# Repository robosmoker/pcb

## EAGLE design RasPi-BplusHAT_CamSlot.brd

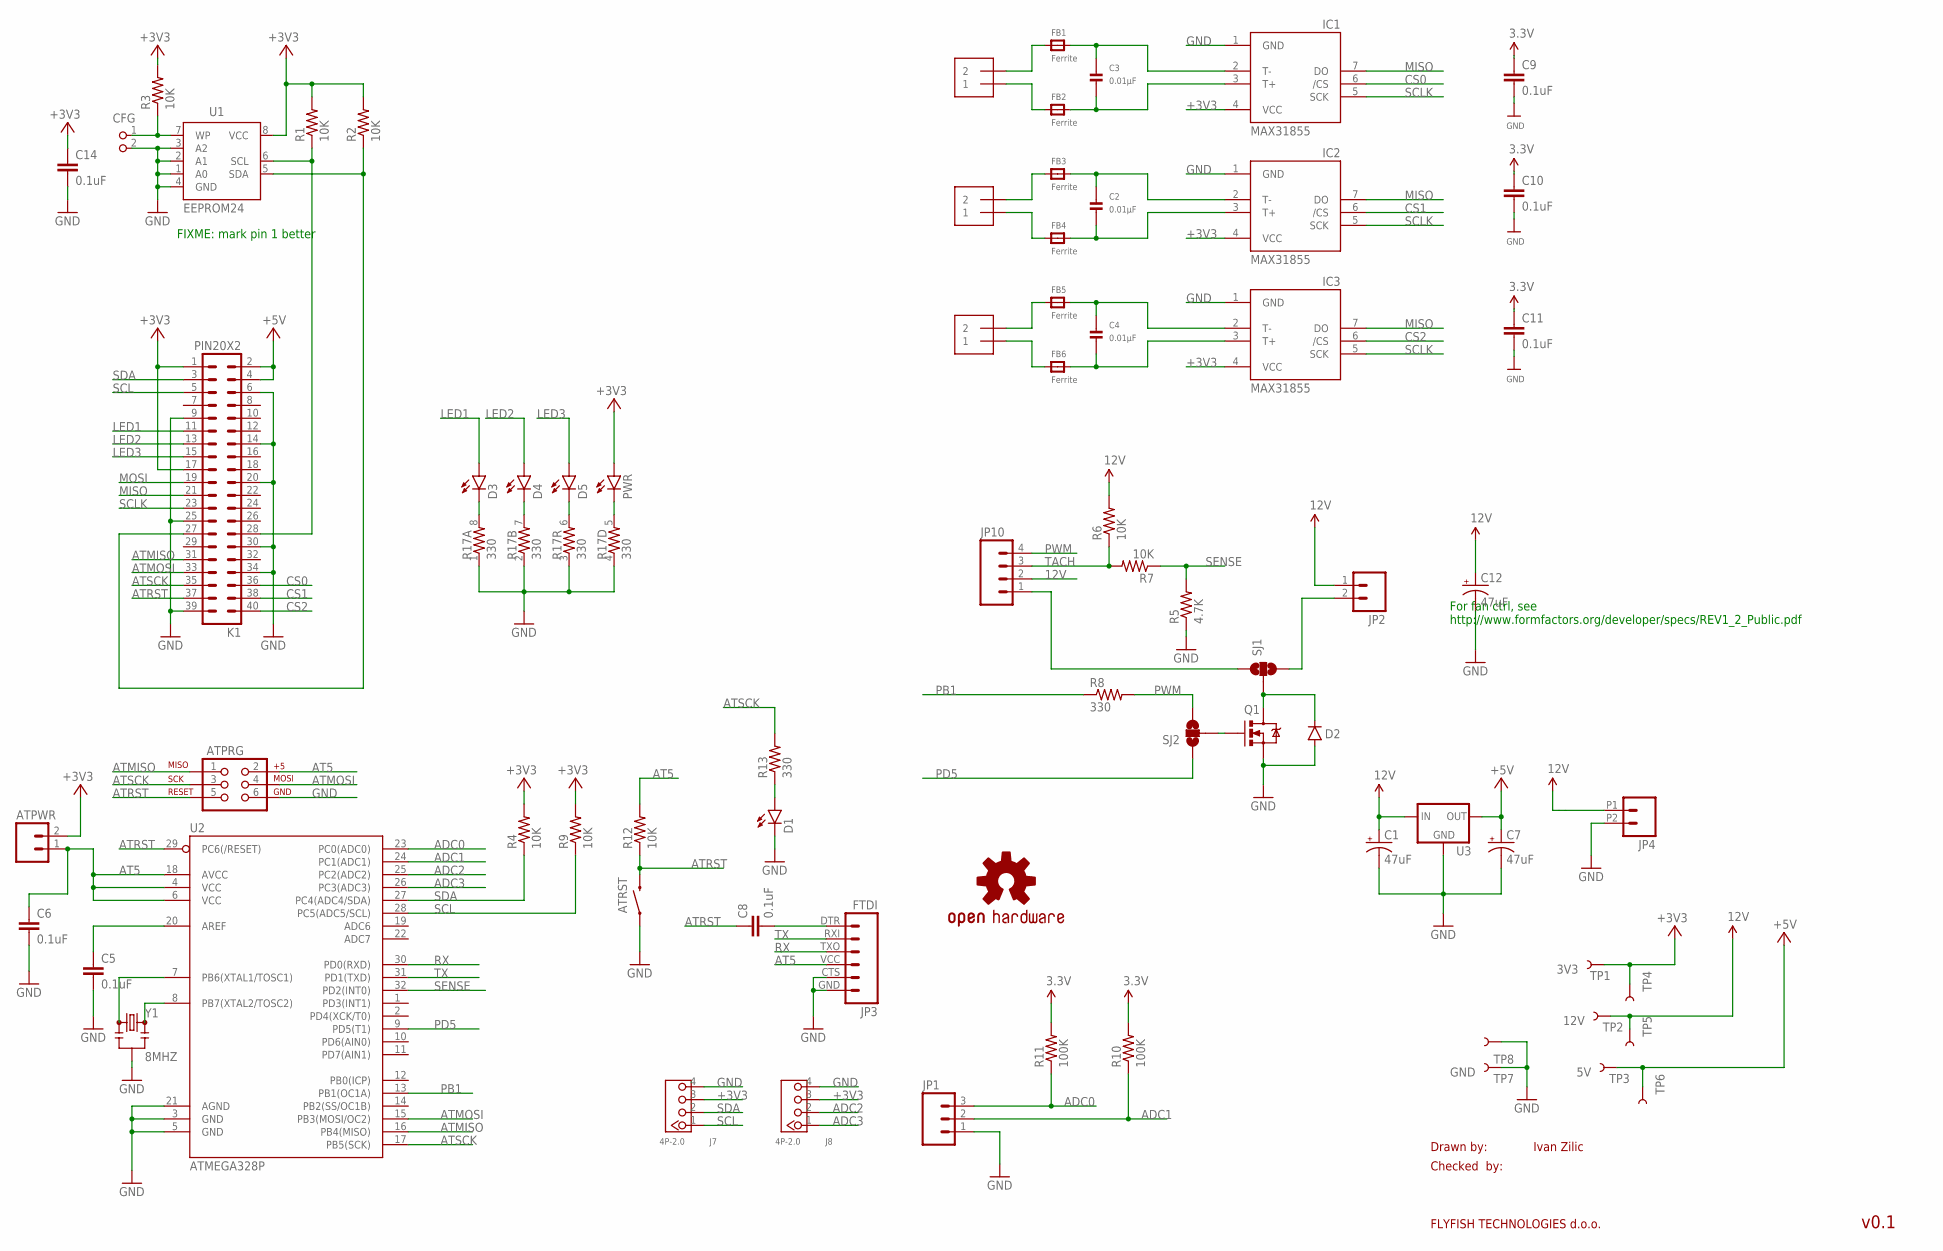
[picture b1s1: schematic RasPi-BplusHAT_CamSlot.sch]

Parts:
ATPRG: AVR_SPI_PRG_62X3_LOCK; 2X3_LOCK
ATPWR: M02LOCK; 1X02_LOCK
ATRST: SWITCH-MOMENTARY-2PTH; TACTILE-PTH
C1, C7, C12: 47uF; EIA7343
C2, C3, C4: 0.01µF; _0805
C5, C6, C8: 0.1uF; 0603-CAP
C9, C10, C11, C14: 0.1uF; 0805
CFG: PIN2_100; PIN_W_2
D1, D3, D4, D5: LED0603; LED-0603
D2: 250mA; SOD-323
FB1, FB2, FB3, FB4, FB5, FB6: Ferrite; _0805
IC1, IC2, IC3: MAX31855; SO08
J1, J2, J3: 1X2-3.5MM
J7, J8: 4P-2.0; HW4-2.0
JP1: M03SCREW; SCREWTERMINAL-3.5MM-3
JP2: M02POLAR_LOCK; MOLEX-1X2_LOCK
JP3: FTDI; FTDI_BASIC
JP4: M022.54MM_SCREWTERM; 1X02_2.54_SCREWTERM
JP10: M04POLAR_LOCK; MOLEX-1X4_LOCK
K1: PIN20X2; PIN_20X2
LOGO1: OSHW-LOGOM; OSHW-LOGO-M
PWR: LED0603; LED-0603
Q1: NFET-FDD8780; DPAK
R1, R2, R3, R4, R6, R7, R9, R12: 10K; 0603-RES
R5: 4.7K; 0603-RES
R8, R13: 330; 0603-RES
R10, R11: 100K; 0603-RES
R17: 330; 0603-ARV
SJ1, SJ2: SOLDERJUMPER_2WAYS; SJ_3
TP1: 3V3; PAD.03X.04
TP2: 12V; PAD.03X.04
TP3: 5V; PAD.03X.04
TP4, TP5, TP6, TP8: 3V3; TP_15TH
TP7: GND; PAD.03X.04
U1: EEPROM24; SOIC8
U2: ATMEGA328P; TQFP32-08
U3: V_REG_78XXSINK; TO220-IGO
Y1: 8MHZ; RESONATOR-SMD

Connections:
12V: C1.A (+), C12.A (+), JP2.1, JP4.P1 (1), JP10.2, R6.2, TP2.P$1, TP5.P$1, U3.IN
+3V3: ATPWR.2, C9.1, C10.1, C11.1, C14.1, IC1.4 (VCC), IC2.4 (VCC), IC3.4 (VCC), J7.3, J8.3, K1.1, K1.17, PWR.A, R1.2, R2.2, R3.2, R4.2, R9.2, R10.2, R11.2, TP1.P$1, TP4.P$1, U1.8 (VCC)
+5V: C7.A (+), K1.2, K1.4, TP3.P$1, TP6.P$1, U3.OUT
ADC0: JP1.3, R11.1, U2.23 (PC0(ADC0))
ADC1: JP1.2, R10.1, U2.24 (PC1(ADC1))
ADC2: J8.2, U2.25 (PC2(ADC2))
ADC3: J8.1, U2.26 (PC3(ADC3))
AT5: ATPRG.2, ATPWR.1, C6.1, JP3.VCC (4), R12.2, U2.4 (VCC), U2.6 (VCC), U2.18 (AVCC)
ATMISO: ATPRG.1, K1.31, U2.16 (PB4(MISO))
ATMOSI: ATPRG.4, K1.33, U2.15 (PB3(MOSI/OC2))
ATRST: ATPRG.5, ATRST.3 (2), C8.1, K1.37, R12.1, U2.29 (PC6(/RESET))
ATSCK: ATPRG.3, K1.35, R13.2, U2.17 (PB5(SCK))
CS0: IC1.6 (/CS), K1.36
CS1: IC2.6 (/CS), K1.38
CS2: IC3.6 (/CS), K1.40
GND: ATPRG.6, ATRST.1, C1.C (-), C5.2, C6.2, C7.C (-), C9.2, C10.2, C11.2, C12.C (-), C14.2, CFG.2, D1.C, D2.A, IC1.1 (GND), IC2.1 (GND), IC3.1 (GND), J7.4, J8.4, JP1.1, JP3.CTS (5), JP3.GND (6), JP4.P2 (2), K1.6, K1.9, K1.14, K1.20, K1.25, K1.30, K1.34, K1.39, Q1.3 (S), R5.1, R17.1, R17.2 (1), R17.3 (1), R17.4 (1), TP7.P$1, TP8.P$1, U1.1 (A0), U1.2 (A1), U1.3 (A2), U1.4 (GND), U2.3 (GND), U2.5 (GND), U2.21 (AGND), U3.GND, Y1.2
LED1: D3.A, K1.11
LED2: D4.A, K1.13
LED3: D5.A, K1.15
MISO: IC1.7 (DO), IC2.7 (DO), IC3.7 (DO), K1.21
MOSI: K1.19
unnamed: K1.28, R1.1, U1.6 (SCL)
unnamed: K1.27, R2.1, U1.5 (SDA)
unnamed: CFG.1, R3.1, U1.7 (WP)
unnamed: FB1.1, J1.2
unnamed: C3.1, FB1.2, IC1.2 (T-)
unnamed: FB2.1, J1.1
unnamed: C3.2, FB2.2, IC1.3 (T+)
unnamed: FB3.1, J2.2
unnamed: C2.1, FB3.2, IC2.2 (T-)
unnamed: FB4.1, J2.1
unnamed: C2.2, FB4.2, IC2.3 (T+)
unnamed: FB5.1, J3.2
unnamed: C4.1, FB5.2, IC3.2 (T-)
unnamed: FB6.1, J3.1
unnamed: C4.2, FB6.2, IC3.3 (T+)
unnamed: JP2.2, SJ1.3
unnamed: JP10.1, SJ1.1
unnamed: C5.1, U2.20 (AREF)
unnamed: C8.2, JP3.DTR (1)
unnamed: D1.A, R13.1
unnamed: D3.C, R17.8 (2)
unnamed: D2.C, Q1.4 (D), SJ1.2
unnamed: D4.C, R17.7 (2)
unnamed: D5.C, R17.6 (2)
unnamed: Q1.1 (G), SJ2.2
unnamed: U2.7 (PB6(XTAL1/TOSC1)), Y1.1
unnamed: U2.8 (PB7(XTAL2/TOSC2)), Y1.3
PB1: R8.1, U2.13 (PB1(OC1A))
PD5: SJ2.1, U2.9 (PD5(T1))
PWM: JP10.4, R8.2, SJ2.3
PWR: PWR.C, R17.5 (2)
RX: JP3.TXO (3), U2.30 (PD0(RXD))
SCL: J7.1, K1.5, R9.1, U2.28 (PC5(ADC5/SCL))
SCLK: IC1.5 (SCK), IC2.5 (SCK), IC3.5 (SCK), K1.23
SDA: J7.2, K1.3, R4.1, U2.27 (PC4(ADC4/SDA))
SENSE: R5.2, R7.1, U2.32 (PD2(INT0))
TACH: JP10.3, R6.1, R7.2
TX: JP3.RXI (2), U2.31 (PD1(TXD))

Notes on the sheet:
Drawn by:
Checked by:
FLYFISH TECHNOLOGIES d.o.o.
Ivan Zilic
v0.1
For fan ctrl, see http://www.formfactors.org/developer/specs/REV1_2_Public.pdf
FIXME: mark pin 1 better

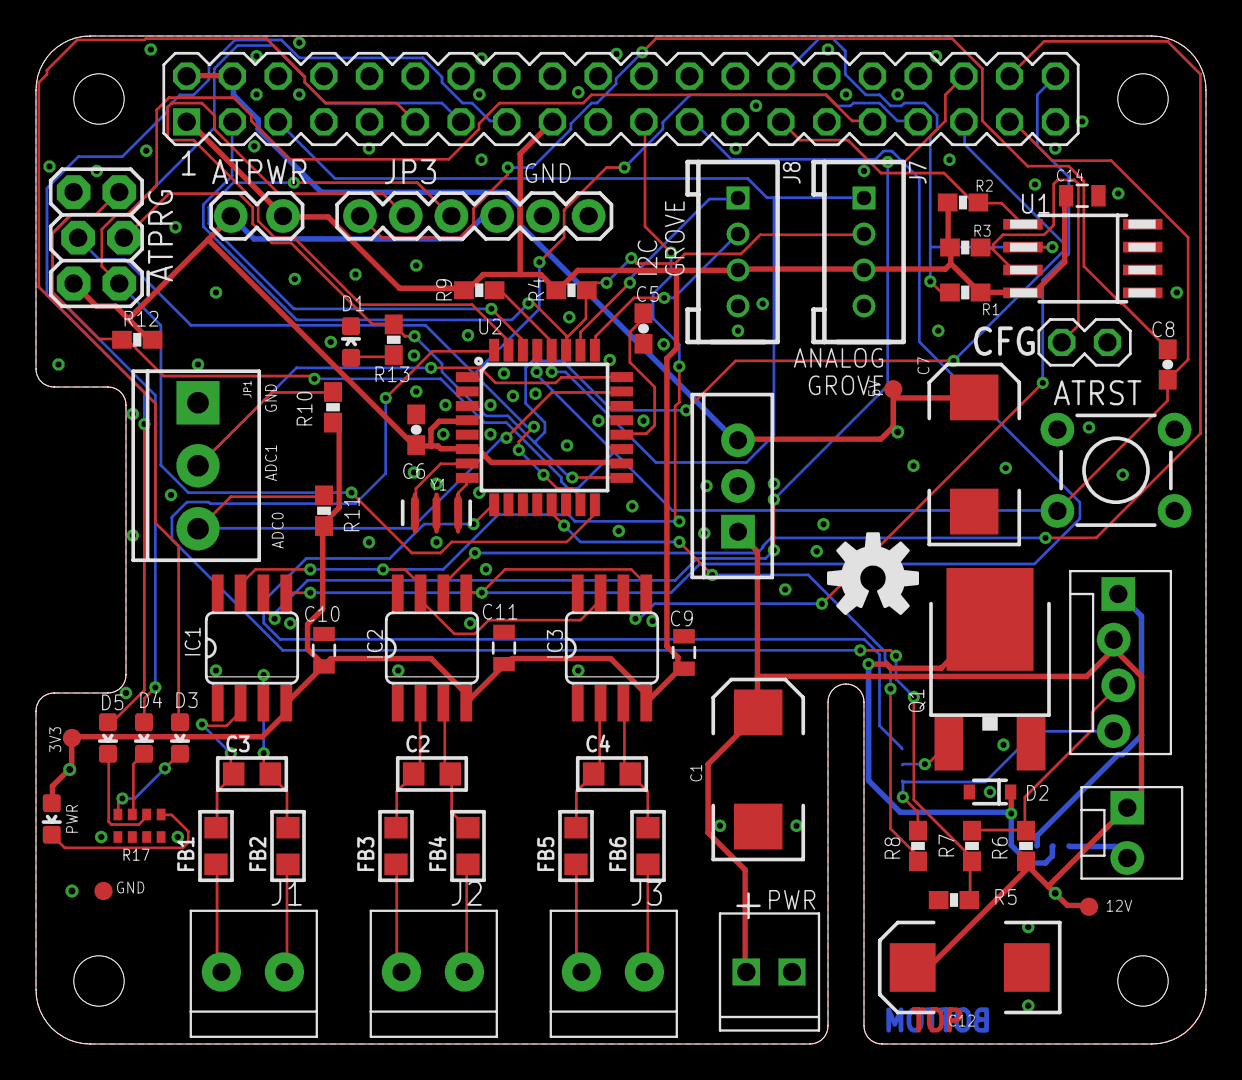
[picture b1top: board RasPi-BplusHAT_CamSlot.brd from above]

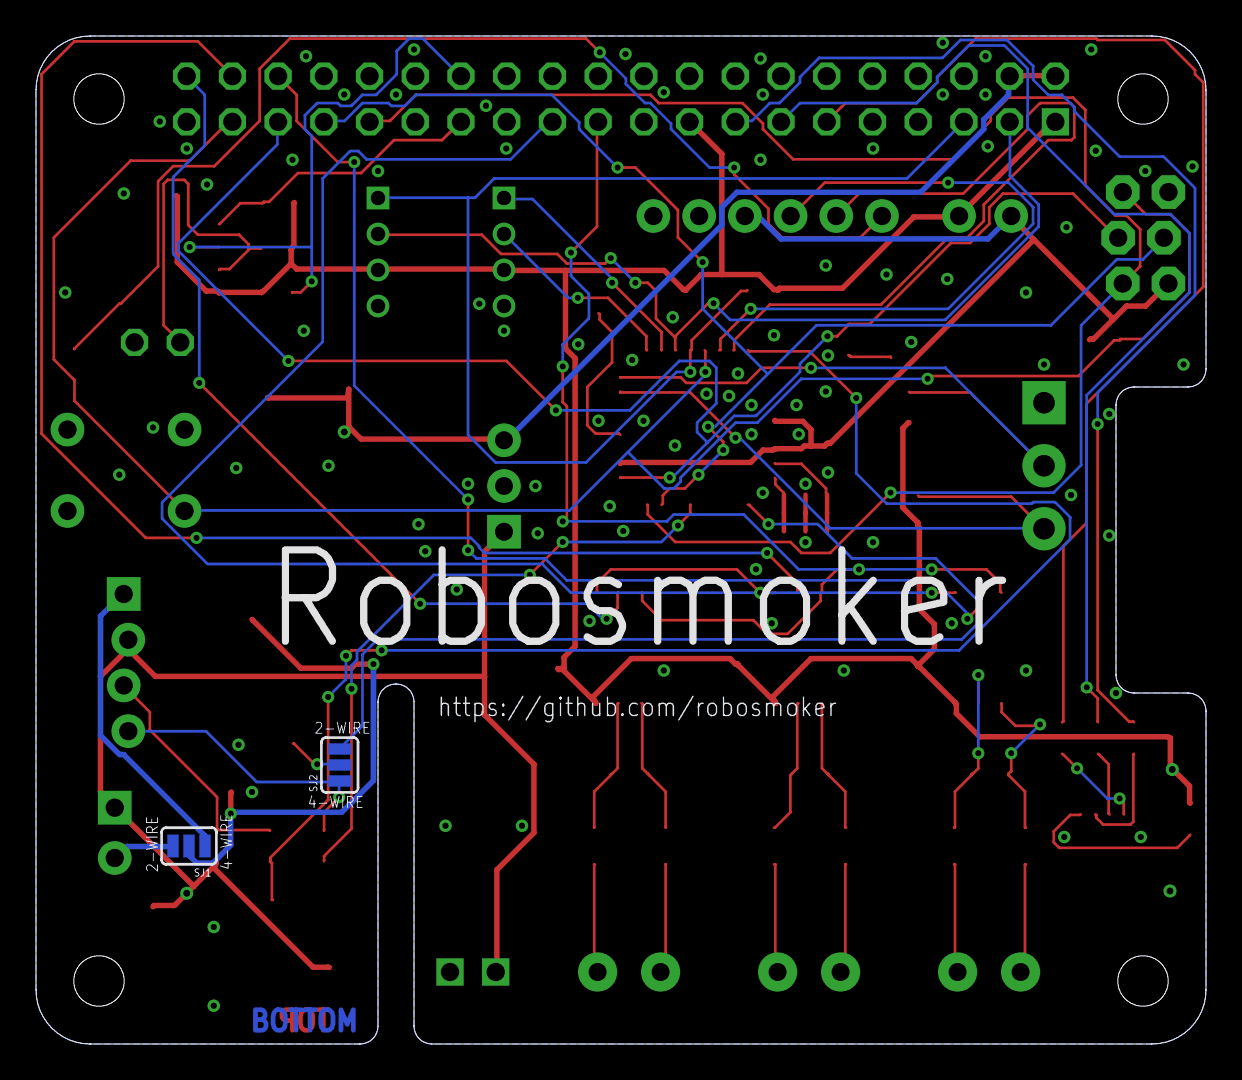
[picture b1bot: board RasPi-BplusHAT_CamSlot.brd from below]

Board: 2 copper layers, 65.0 x 56.0 mm, 73 parts (2 on the bottom side), 58 nets.

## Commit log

2015-12-19 initial commit
    as sent to board house
2016-01-01 some fixmes
2016-01-16 as sent to oshpark for rev2
2016-01-16 tidying up things

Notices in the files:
parts and their libraries:
SparkFun-Passives: Licensing: Creative Commons ShareAlike 4.0 International - https://creativecommons.org/licenses/by-sa/4.0
